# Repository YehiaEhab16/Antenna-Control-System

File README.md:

# Antenna-Control-System

Using Arduino, an antenna is controlled to keep track of a satellite during 4 sessions daily.
The system is used to control the antenna using 2 speeds and in 2 directions

## <a href="https://github.com/AhmedAbo-zeid" target="_blank">Ahmed AboZeid</a>
## Mario Abdelmeseeh
## Mohamed Abdelmegeed
## <a href="https://github.com/Tarek9100" target="_blank">Tarek Wael</a>
## <a href="https://github.com/yehia2000000" target="_blank">Yehia Shahin</a>
## <a href="https://github.com/YehiaEhab16" target="_blank">Yehia Ehab</a>

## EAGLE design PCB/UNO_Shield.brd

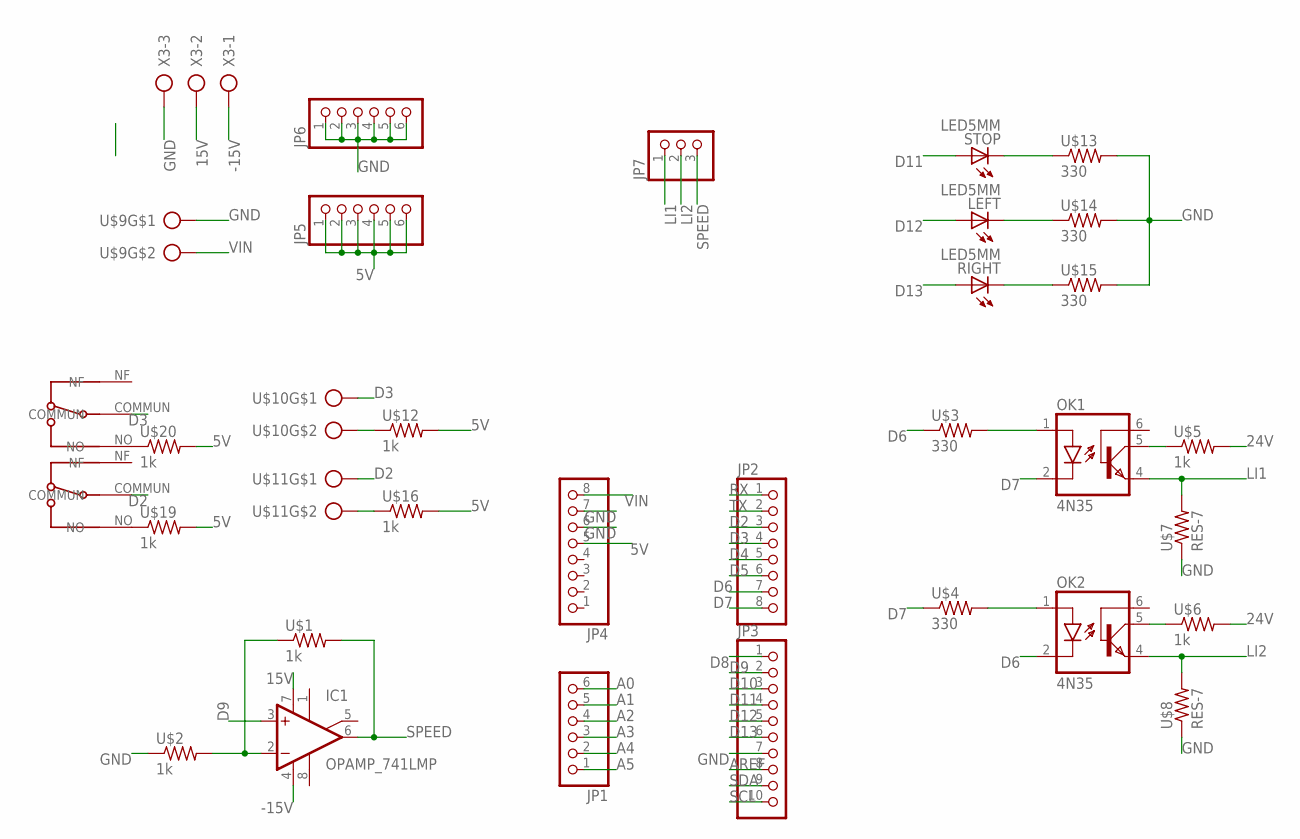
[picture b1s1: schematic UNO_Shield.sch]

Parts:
IC1: OPAMP_741LMP; DIL08
JP1, JP5, JP6: PINHD-1X6; 1X06
JP2, JP4: PINHD-1X8; 1X08
JP3: PINHD-1X10; 1X10
JP7: PINHD-3_DATA; 1X03_DATA
LEFT: LED5MM
OK1, OK2: 4N35; DIL06
RIGHT: LED5MM
STOP: LED5MM
U$1, U$2, U$5, U$6, U$12, U$16, U$19, U$20: 1k; 0204/7
U$3, U$4, U$13, U$14, U$15: 330; 0204/7
U$7, U$8: RES-7; 0204/7
U$9, U$10, U$11: CON_PTR_2; AK300/2
U$17, U$18: MICROSWITCHCOUDE; DG23-B3RA
X3: CON_PTR_3; AK300/3

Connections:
5V: JP4.5, JP5.1, JP5.2, JP5.3, JP5.4, JP5.5, JP5.6, U$12.2, U$16.2, U$19.2, U$20.2
15V: IC1.7 (V+), X3.2
24V: U$5.2, U$6.2
-15V: IC1.4 (V-), X3.1
A0: JP1.6
A1: JP1.5
A2: JP1.4
A3: JP1.3
A4: JP1.2
A5: JP1.1
AREF: JP3.8
D2: JP2.3, U$11.1, U$18.COMMUN
D3: JP2.4, U$10.1, U$17.COMMUN
D4: JP2.5
D5: JP2.6
D6: JP2.7, OK1.1 (A), OK2.2 (C), U$3.1, U$3.2
D7: JP2.8, OK1.2 (C), OK2.1 (A), U$4.1, U$4.2
D8: JP3.1
D9: IC1.3 (+IN), JP3.2
D10: JP3.3
D11: JP3.4, STOP.A
D12: JP3.5, LEFT.A
D13: JP3.6, RIGHT.A
GND: JP3.7, JP4.6, JP4.7, JP6.1, JP6.2, JP6.3, JP6.4, JP6.5, JP6.6, U$2.1, U$7.1, U$8.1, U$9.1, U$13.2, U$14.2, U$15.2, X3.3
LI1: JP7.1, OK1.4 (EMI), U$7.2
LI2: JP7.2, OK2.4 (EMI), U$8.2
unnamed: IC1.2 (-IN), U$1.1, U$2.2
unnamed: OK1.5 (COL), U$5.1
unnamed: U$10.2, U$12.1
unnamed: STOP.K (C), U$13.1
unnamed: U$11.2, U$16.1
unnamed: U$18.NO, U$19.1
unnamed: U$17.NO, U$20.1
unnamed: LEFT.K (C), U$14.1
unnamed: OK2.5 (COL), U$6.1
unnamed: RIGHT.K (C), U$15.1
RX: JP2.1
SCL: JP3.10
SDA: JP3.9
SPEED: IC1.6 (OUT), JP7.3, U$1.2
TX: JP2.2
VIN: JP4.8, U$9.2

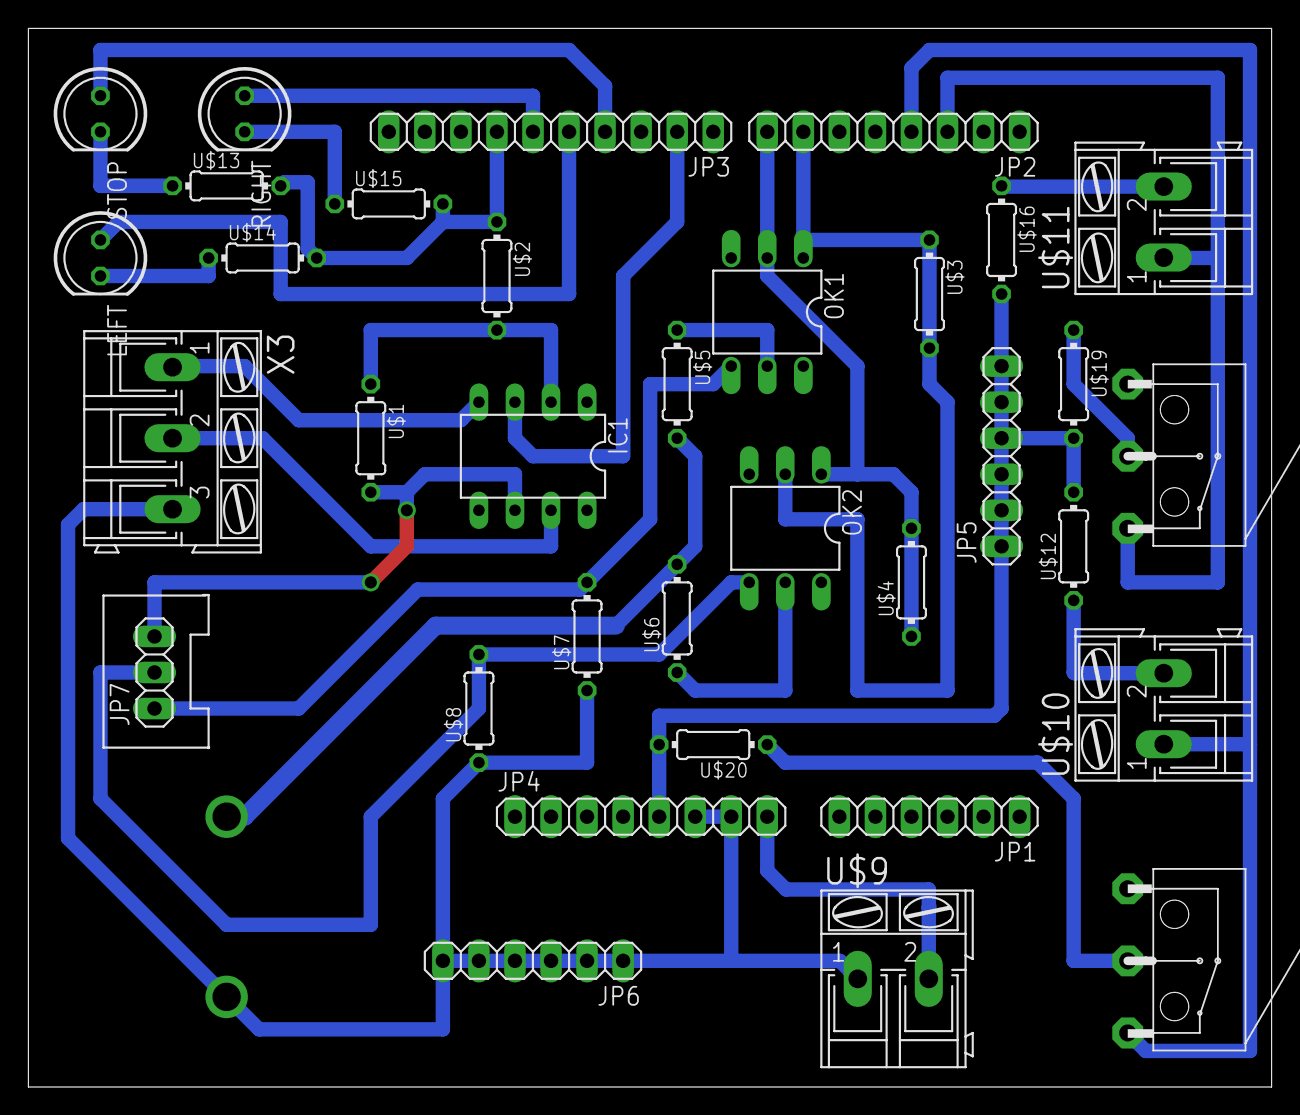
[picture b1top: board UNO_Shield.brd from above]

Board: 2 copper layers, 87.6 x 74.6 mm, 34 parts (0 on the bottom side), 27 nets.

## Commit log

2021-08-23 Create Labview
2022-01-08 Organizing Directories
2022-01-08 Final GUI Version
